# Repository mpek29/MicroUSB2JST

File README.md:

# MicroUSB2JST

## 🚀 Overview

**MicroUSB2JST** is an open-source PCB that acts as a bridge between a Micro USB port and JST connectors (JST-SH and JST-PH). This module is designed to simplify connections for embedded projects, prototyping, and power distribution.

## 🎯 Purpose
- 🔌 **Convenient power and data interface**: Easily connect USB power or data lines to JST-equipped devices.
- 📏 **Compact and Adafruit-compatible**: Designed to fit within Adafruit's standard PCB footprint.
- 🛠️ **Open-source and customizable**: Modify and adapt the design to suit your specific needs.

## 📝 Features
| 🏷️ Feature       | 🔍 Description |
|----------------|-------------|
| 🔌 **Connector 1** | Micro USB (⚡ power & 🔄 data) |
| 🔌 **Connector 2** | JST-PH (⚡ higher current capacity) |
| 🔌 **Connector 3** | JST-SH (📏 small form factor) |
| 🖥️ **PCB Design**  | 🆓 Open-source & ✏️ customizable |
| 🎯 **Use Cases**   | ⚡ Power distribution, 🛰️ sensor connections, 🤖 embedded systems 

## 📐 PCB Design Preview
| 📜 Schematic | 🖥️ PCB Layout | 🏗️ 3D |
|-----------|-----------|-----------|
|  |  |  |

## 🌟 License
This project is open-source. Feel free to use, modify, and contribute! 🚀

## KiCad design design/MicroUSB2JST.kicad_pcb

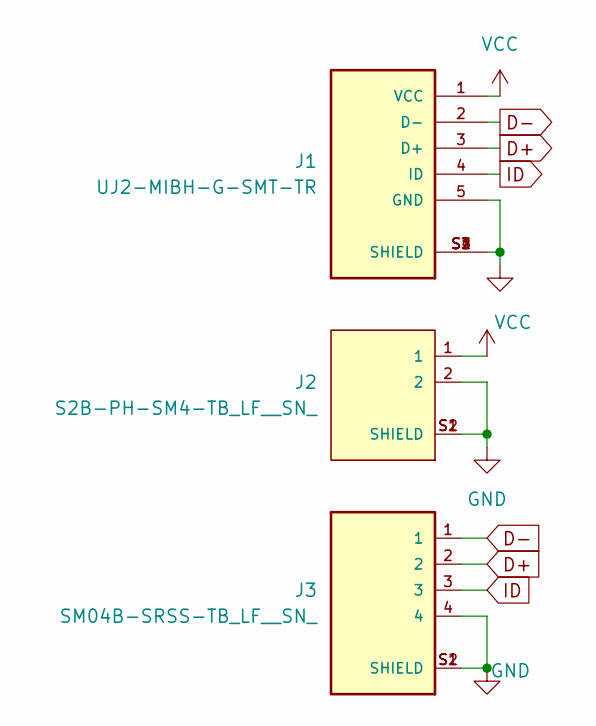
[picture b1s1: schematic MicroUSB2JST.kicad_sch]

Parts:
J1: UJ2-MIBH-G-SMT-TR; CUI_UJ2-MIBH-G-SMT-TR; PARTREV 1.0
J2: S2B-PH-SM4-TB_LF__SN_; JST_S2B-PH-SM4-TB_LF__SN_
J3: SM04B-SRSS-TB_LF__SN_; JST_SM04B-SRSS-TB_LF__SN_

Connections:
D+: J1.3 (D+), J3.2
D-: J1.2 (D-), J3.1
GND: J1.5 (GND), J1.S1 (SHIELD), J1.S2 (SHIELD), J1.S3 (SHIELD), J1.S4 (SHIELD), J2.2, J2.S1 (SHIELD), J2.S2 (SHIELD), J3.4, J3.S1 (SHIELD), J3.S2 (SHIELD)
ID: J1.4 (ID), J3.3
VCC: J1.1 (VCC), J2.1

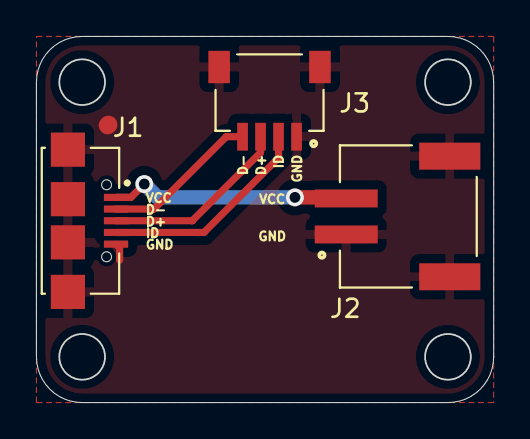
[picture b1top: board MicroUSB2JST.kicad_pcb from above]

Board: 2 copper layers, 25.4 x 20.3 mm, 3 parts (0 on the bottom side), 5 nets.

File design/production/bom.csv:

Designator,Footprint,Quantity,Value,LCSC Part #
J1,CUI_UJ2-MIBH-G-SMT-TR,1,UJ2-MIBH-G-SMT-TR,
J2,JST_S2B-PH-SM4-TB_LF__SN_,1,S2B-PH-SM4-TB_LF__SN_,
J3,JST_SM04B-SRSS-TB_LF__SN_,1,SM04B-SRSS-TB_LF__SN_,

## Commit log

2025-02-19 Addition of some images to better describe the project
2025-03-03 best adaptation to adafruit swirly grill
2025-04-10 adjustement and gerber files
